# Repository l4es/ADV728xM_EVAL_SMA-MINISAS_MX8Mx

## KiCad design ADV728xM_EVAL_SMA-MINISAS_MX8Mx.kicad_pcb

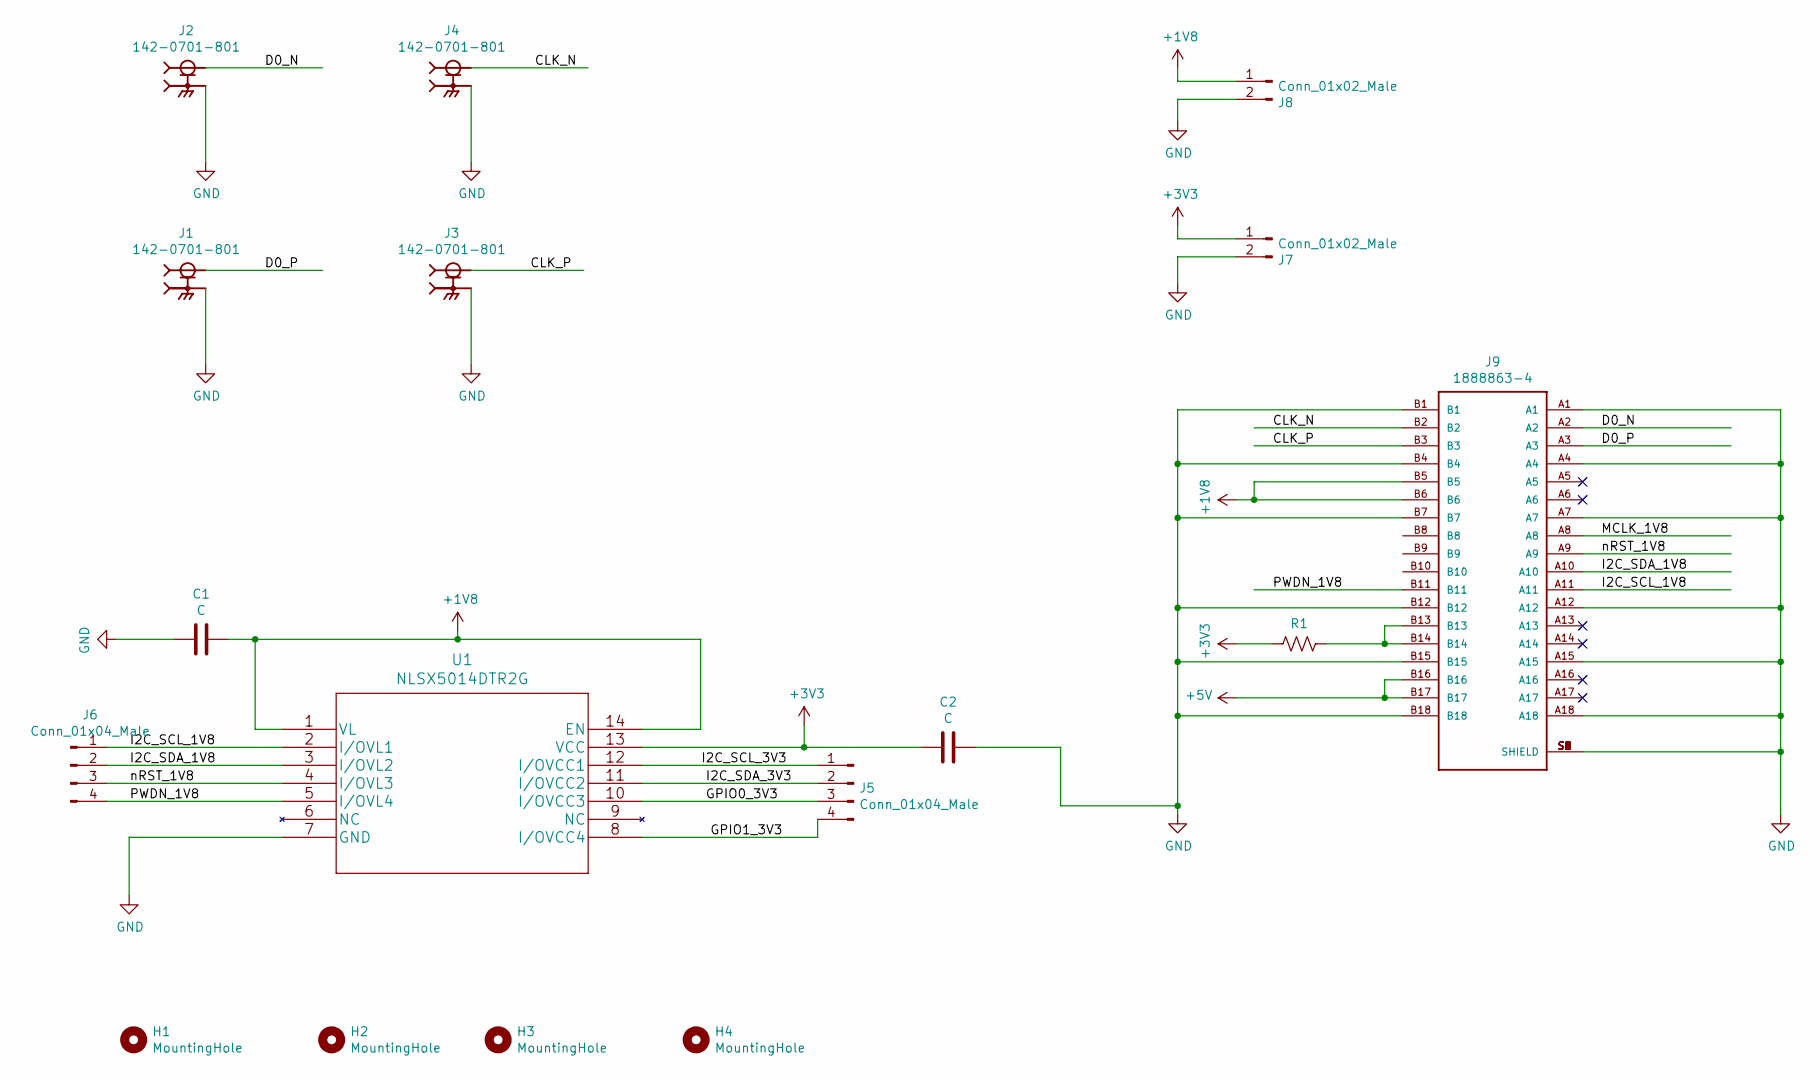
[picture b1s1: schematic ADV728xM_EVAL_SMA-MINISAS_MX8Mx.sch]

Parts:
C1, C2: C; C_0603_1608Metric_Pad1.08x0.95mm_HandSolder
H1, H2, H3, H4: MountingHole; MountingHole_3.2mm_M3
J1, J2, J3, J4: 142-0701-801; CINCH_142-0701-801; PARTREV N/A
J5, J6: Conn_01x04_Male; PinHeader_1x04_P2.54mm_Vertical
J7, J8: Conn_01x02_Male; PinHeader_1x02_P2.54mm_Vertical
J9: 1888863-4; TE_1888863-4
R1: 0; R_0805_2012Metric_Pad1.20x1.40mm_HandSolder
U1: NLSX5014DTR2G

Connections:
+1V8: C1.2, J8.1, J9.B5, J9.B6, U1.1 (VL), U1.14 (EN)
+3V3: C2.2, J7.1, R1.2, U1.13 (VCC)
+5V: J9.B16, J9.B17
/CLK_N: J4.1, J9.B2
/CLK_P: J3.1, J9.B3
/D0_N: J2.1, J9.A2
/D0_P: J1.1, J9.A3
/GPIO0_3V3: J5.3, U1.10 (I/OVCC3)
/GPIO1_3V3: J5.4, U1.8 (I/OVCC4)
/I2C_SCL_1V8: J6.1, J9.A11, U1.2 (I/OVL1)
/I2C_SCL_3V3: J5.1, U1.12 (I/OVCC1)
/I2C_SDA_1V8: J6.2, J9.A10, U1.3 (I/OVL2)
/I2C_SDA_3V3: J5.2, U1.11 (I/OVCC2)
/MCLK_1V8: J9.A8
/PWDN_1V8: J6.4, J9.B11, U1.5 (I/OVL4)
/nRST_1V8: J6.3, J9.A9, U1.4 (I/OVL3)
GND: C1.1, C2.1, J1.S1, J1.S2, J1.S3, J1.S4, J2.S1, J2.S2, J2.S3, J2.S4, J3.S1, J3.S2, J3.S3, J3.S4, J4.S1, J4.S2, J4.S3, J4.S4, J7.2, J8.2, J9.A1, J9.A4, J9.A7, J9.A12, J9.A15, J9.A18, J9.B1, J9.B4, J9.B7, J9.B12, J9.B15, J9.B18, J9.S1 (SHIELD), J9.S2 (SHIELD), J9.S3 (SHIELD), J9.S4 (SHIELD), J9.S5 (SHIELD), J9.S6 (SHIELD), J9.S7 (SHIELD), J9.S8 (SHIELD), U1.7 (GND)
unnamed: J9.B13, J9.B14, R1.1

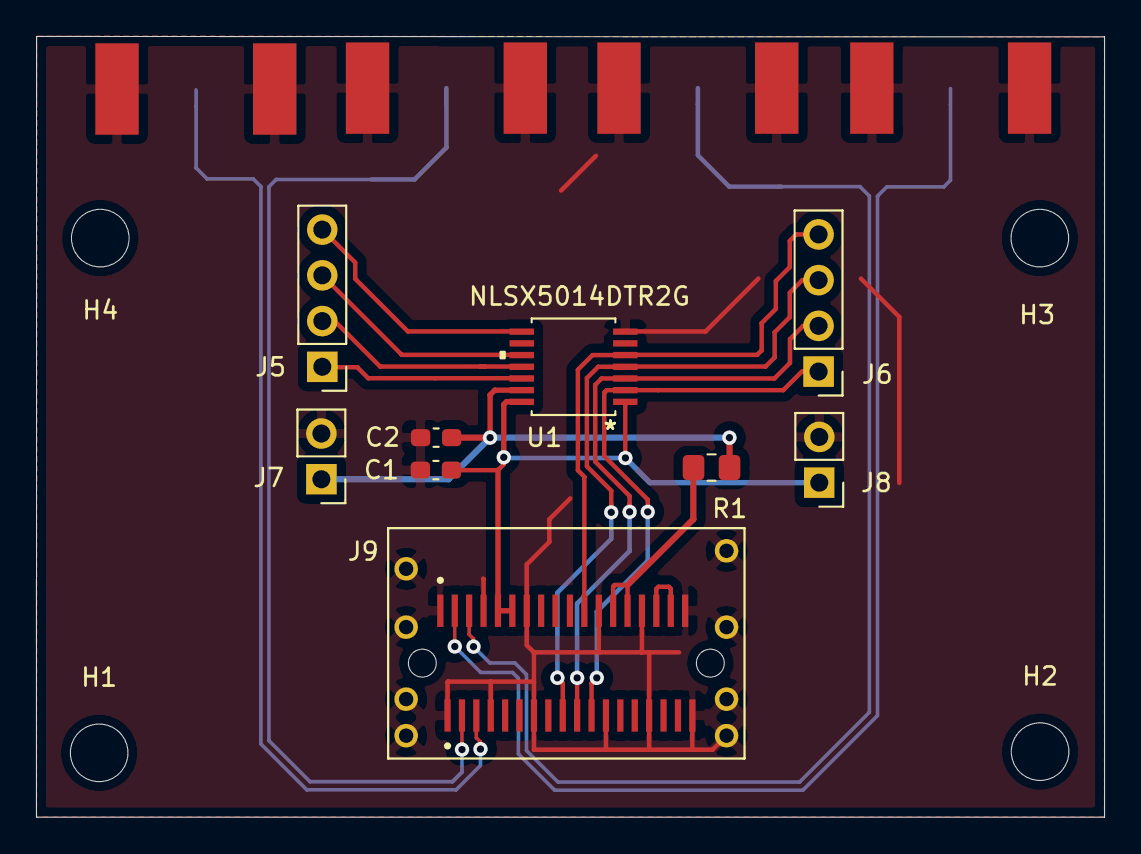
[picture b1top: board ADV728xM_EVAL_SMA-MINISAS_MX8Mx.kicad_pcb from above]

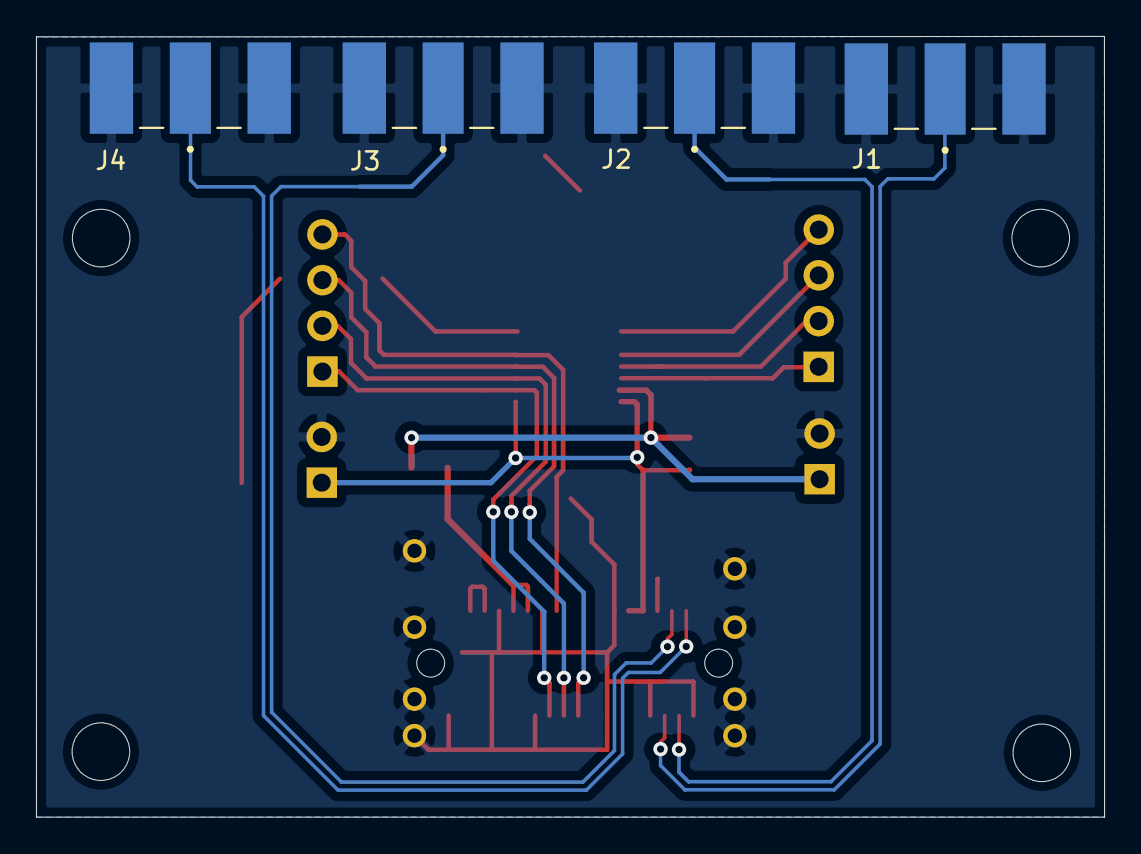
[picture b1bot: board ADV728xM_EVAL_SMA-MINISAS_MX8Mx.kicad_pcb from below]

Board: 2 copper layers, 59.3 x 43.4 mm, 17 parts (4 on the bottom side), 17 nets.

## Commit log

2021-08-07 Add first production release V1A
2021-08-07 Add unsaved schematic

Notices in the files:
parts and their libraries:
Copyright 2021 Accelerated Designs. All rights reserved.
